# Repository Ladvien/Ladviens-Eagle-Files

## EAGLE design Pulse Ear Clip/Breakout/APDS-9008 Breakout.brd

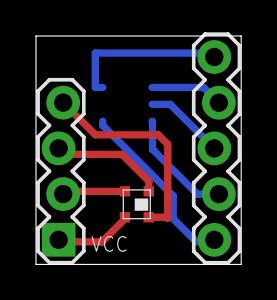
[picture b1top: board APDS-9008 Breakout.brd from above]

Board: 2 copper layers, 11.4 x 12.7 mm, 4 parts (1 on the bottom side), 9 nets.

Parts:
JP1: 1X04_LOCK
JP2: 1X05_LOCK
U$1: APDS9008
U$2: MCP6001UT-E/OT; SOT95P270X145-5N

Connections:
A-GND: JP1.3, U$1.GND
A-NC: JP1.4, U$1.NCC1
A-OUT: JP1.2, U$1.OUT
A-VCC: JP1.1, U$1.VCC
M-VDD: JP2.5, U$2.5
M-VIN+: JP2.2, U$2.3
M-VIN-: JP2.1, U$2.4
M-VOUT: JP2.4, U$2.1
M-VSS: JP2.3, U$2.2

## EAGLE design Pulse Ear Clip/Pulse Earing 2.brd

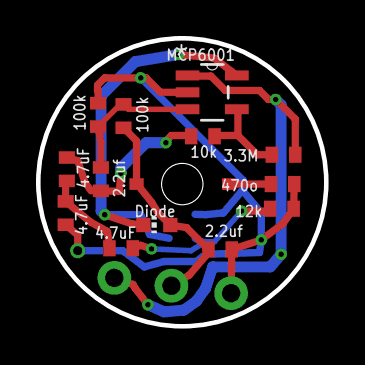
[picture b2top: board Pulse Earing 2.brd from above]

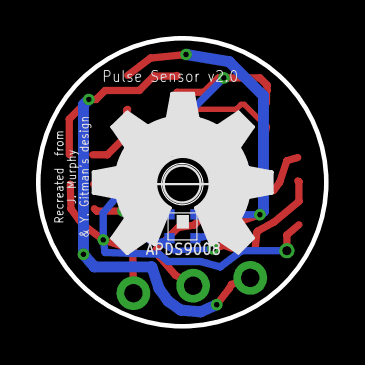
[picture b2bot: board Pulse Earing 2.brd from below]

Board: 2 copper layers, 16.0 x 16.0 mm, 19 parts (3 on the bottom side), 10 nets.

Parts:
+V: M01SMDNS; 1X01NS
C1, C4: 2.2uf; C0402
C2, C3, C5: 4.7uf; C0402
GND: M01SMDNS; 1X01NS
LED1: CHIP-LED0603
OUT: M01SMDNS; 1X01NS
R1: 10k; R0402
R2, R3: 100k; R0402
R4: 12k; R0402
R5: 470; R0402
R6: 3.3m; R0402
U$1: MCP6001UT-E/OT; SOT95P270X145-5N
U$2: APDS9008
U$3: KBREVMTNLED; KBREVMNTLED
U$4: OSHW_FILLX350_NOTEXT

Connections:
+V: +V.1, C1.1, LED1.A, R2.2, U$3.V+
unnamed: LED1.C, U$1.5, U$2.VCC
unnamed: R1.2, R6.1, U$1.4
unnamed: C2.1, R4.2, U$2.OUT
unnamed: C2.2, C3.1, C5.1
unnamed: C3.2, C4.1, R1.1
unnamed: C4.2, R2.1, R3.2, U$1.3
unnamed: R5.2, U$3.GND
unnamed: C1.2, C5.2, GND.1, R3.1, R4.1, R5.1, U$1.2, U$2.GND
OUT: OUT.1, R6.2, U$1.1

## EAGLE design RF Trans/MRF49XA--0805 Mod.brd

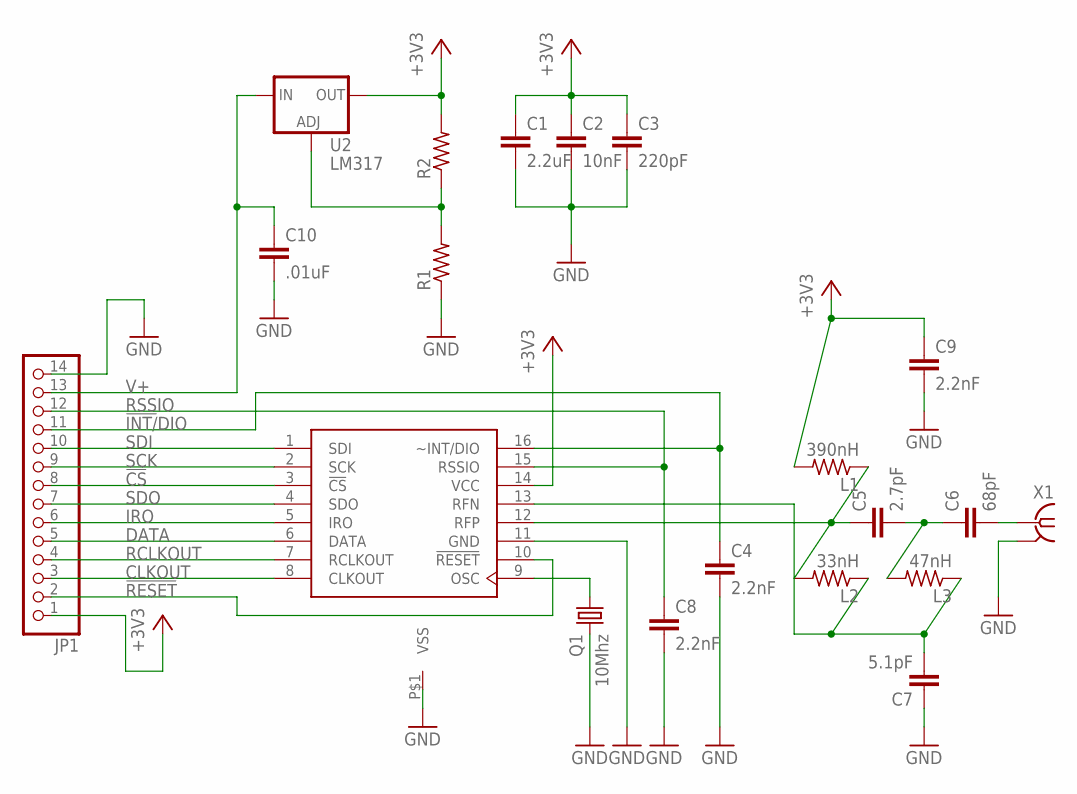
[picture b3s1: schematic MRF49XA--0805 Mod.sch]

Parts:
C1: 2.2uF; C0805
C2: 10nF; C0805
C3: 220pF; C0805
C4, C8, C9: 2.2nF; C0805
C5: 2.7pF; C0805
C6: 68pF; C0805
C7: 5.1pF; C0805
C10: .01uF; C0805
JP1: PINHD-1X14; 1X14
L1: 390nH; R0805
L2: 33nH; R0805
L3: 47nH; R0805
Q1: 10Mhz; CTS406
R1, R2: R-US_M0805; M0805
U2: LM317; SOT223
U$1: MRF49XA; TSSOP16
X1: SMA-142-0701-871/876; J502-ND-142-0701-871/876

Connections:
!CS: JP1.8, U$1.3 (!CS)
!INT/!DIO: C4.1, JP1.11, U$1.16 (~INT/DIO)
!RESET: JP1.2, U$1.10 (!RESET)
+3V3: C1.1, C2.1, C3.1, C9.1, JP1.1, L1.2, R2.2, U2.2 (OUT), U$1.14 (VCC)
CLKOUT: JP1.3, U$1.8 (CLKOUT)
DATA: JP1.5, U$1.6 (DATA)
GND: C1.2, C2.2, C3.2, C4.2, C7.1, C8.2, C9.2, C10.2, JP1.14, Q1.3 (2), R1.1, U$1.11 (GND), U$1.P$1 (VSS), X1.G@1 (GND), X1.G@2 (GND), X1.G@3 (GND), X1.G@4 (GND)
IRO: JP1.6, U$1.5 (IRO)
unnamed: Q1.1, U$1.9 (OSC)
unnamed: C5.2, C6.1, L3.2
unnamed: C6.2, X1.1
unnamed: C7.2, L2.1, L3.1, U$1.13 (RFN)
unnamed: C5.1, L1.1, L2.2, U$1.12 (RFP)
unnamed: R1.2, R2.1, U2.1 (ADJ)
RCLKOUT: JP1.4, U$1.7 (RCLKOUT)
RSSIO: C8.1, JP1.12, U$1.15 (RSSIO)
SCK: JP1.9, U$1.2 (SCK)
SDI: JP1.10, U$1.1 (SDI)
SDO: JP1.7, U$1.4 (SDO)
V+: C10.1, JP1.13, U2.3 (IN)

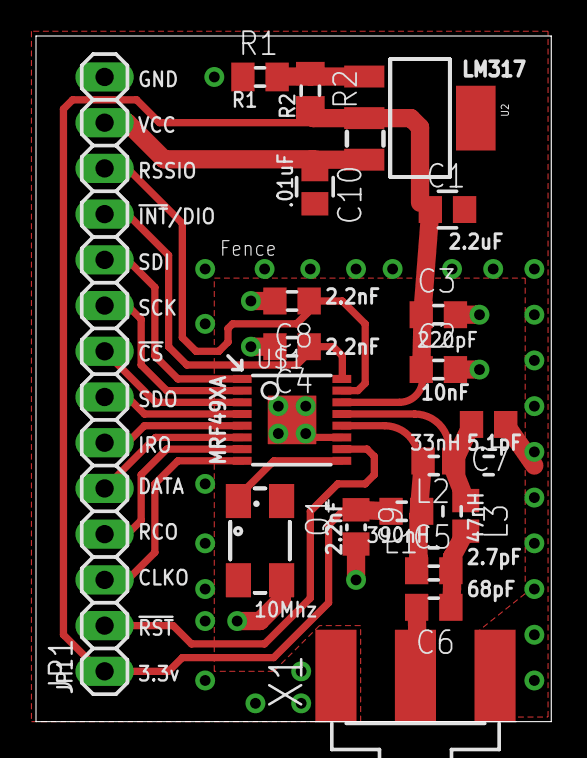
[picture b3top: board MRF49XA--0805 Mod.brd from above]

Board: 2 copper layers, 28.6 x 38.1 mm, 20 parts (0 on the bottom side), 20 nets.

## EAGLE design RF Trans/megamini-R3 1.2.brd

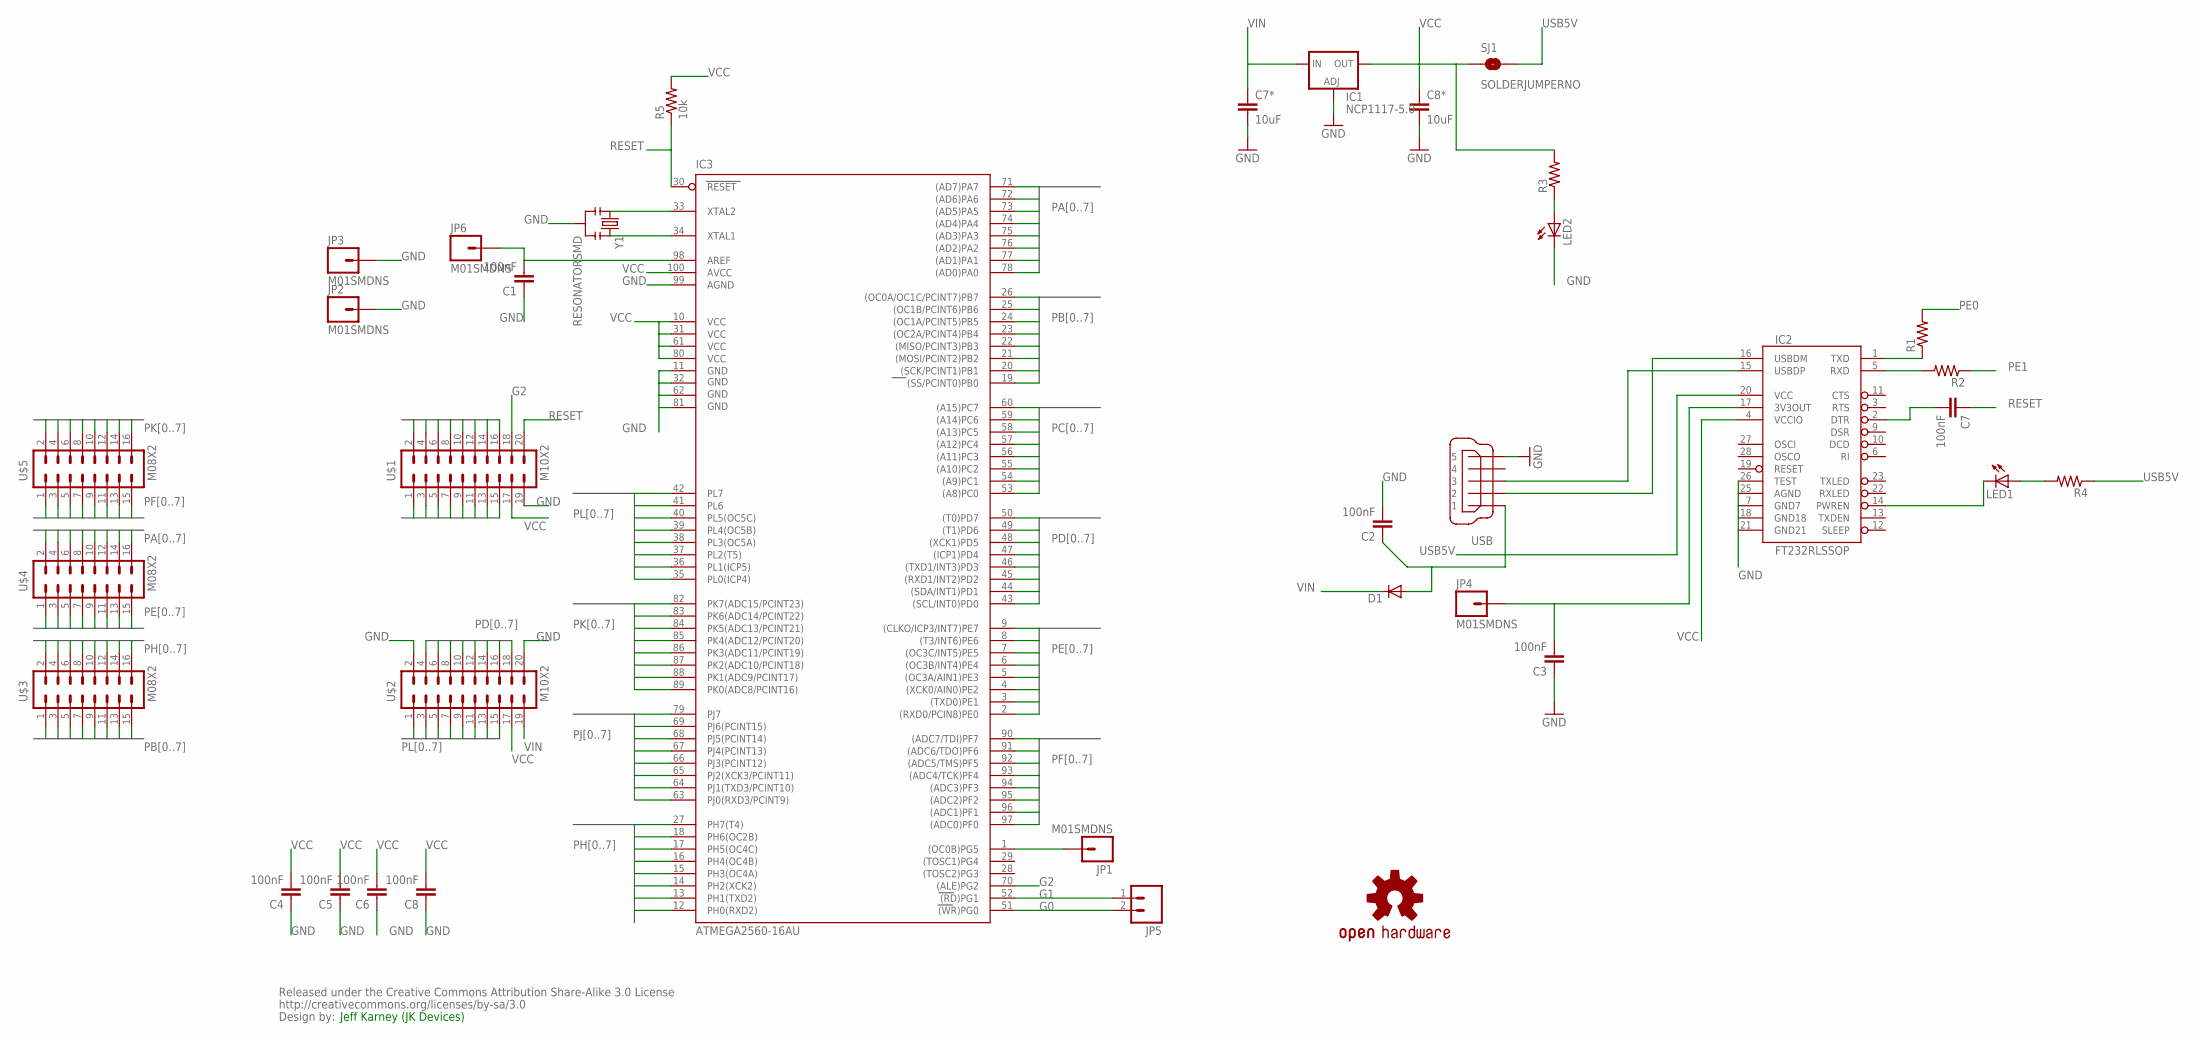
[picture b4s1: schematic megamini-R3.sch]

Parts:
C1, C2, C3, C4, C5, C6, C7, C8: 100nF; 0805
C7*, C8*: 10uF; 0805
D1: DIODESOD; SOD-323
IC1: NCP1117-5.0; DPACK
IC2: FT232RLSSOP; SSOP28DB
IC3: ATMEGA2560-16AU; TQFP100
JP1, JP2, JP3, JP4, JP6: M01SMDNS; 1X01NS
JP5: M02PTH; 1X02
LED1, LED2: LED0603; LED-0603
R1, R2, R3, R4: RESISTOR0805-RES; 0805
R5: 10k; 0805
SJ1: SOLDERJUMPERNO; SJ_2S-NO
U$1, U$2: M10X2; 2X10
U$3, U$4, U$5: M08X2; 2X8_SMALL
U$6: OSHW-LOGOS; OSHW-LOGO-S
U$7: CREATIVE_COMMONS
USB: MINI-USB-UX60-MB-5ST; UX60-MB-5ST
Y1: RESONATORSMD; RESONATOR-SMD

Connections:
G0: IC3.51 ((WR)PG0), JP5.2
G1: IC3.52 ((RD)PG1), JP5.1
G2: IC3.70 ((ALE)PG2), U$1.18
GND: C1.1, C2.2, C3.1, C4.1, C5.1, C6.1, C7*.2, C8.1, C8*.2, IC1.1 (ADJ), IC2.7 (GND7), IC2.18 (GND18), IC2.21 (GND21), IC2.25 (AGND), IC2.26 (TEST), IC3.11 (GND), IC3.32 (GND1), IC3.62 (GND2), IC3.81 (GND3), IC3.99 (AGND), JP2.1, JP3.1, LED2.C, U$1.19, U$2.2, U$2.20, USB.5, Y1.2
unnamed: IC2.16 (USBDM), USB.2
unnamed: IC3.1 ((OC0B)PG5), JP1.1
unnamed: IC2.15 (USBDP), USB.3
unnamed: C7.2, IC2.2 (DTR)
unnamed: IC2.1 (TXD), R1.1
unnamed: IC2.5 (RXD), R2.2
unnamed: C3.2, IC2.17 (3V3OUT), JP4.1
unnamed: IC3.33 (XTAL2), Y1.1
unnamed: IC3.34 (XTAL1), Y1.3
unnamed: LED2.A, R3.1
unnamed: LED1.A, R4.2
unnamed: IC2.14 (PWREN), LED1.C
unnamed: C1.2, IC3.98 (AREF), JP6.1
PA0: IC3.78 ((AD0)PA0), U$4.2
PA1: IC3.77 ((AD1)PA1), U$4.4
PA2: IC3.76 ((AD2)PA2), U$4.6
PA3: IC3.75 ((AD3)PA3), U$4.8
PA4: IC3.74 ((AD4)PA4), U$4.10
PA5: IC3.73 ((AD5)PA5), U$4.12
PA6: IC3.72 ((AD6)PA6), U$4.14
PA7: IC3.71 ((AD7)PA7), U$4.16
PB0: IC3.19 ((SS/PCINT0)PB0), U$3.15
PB1: IC3.20 ((SCK/PCINT1)PB1), U$3.13
PB2: IC3.21 ((MOSI/PCINT2)PB2), U$3.11
PB3: IC3.22 ((MISO/PCINT3)PB3), U$3.9
PB4: IC3.23 ((OC2A/PCINT4)PB4), U$3.7
PB5: IC3.24 ((OC1A/PCINT5)PB5), U$3.5
PB6: IC3.25 ((OC1B/PCINT6)PB6), U$3.3
PB7: IC3.26 ((OC0A/OC1C/PCINT7)PB7), U$3.1
PC0: IC3.53 ((A8)PC0), U$1.15
PC1: IC3.54 ((A9)PC1), U$1.13
PC2: IC3.55 ((A10)PC2), U$1.11
PC3: IC3.56 ((A11)PC3), U$1.9
PC4: IC3.57 ((A12)PC4), U$1.7
PC5: IC3.58 ((A13)PC5), U$1.5
PC6: IC3.59 ((A14)PC6), U$1.3
PC7: IC3.60 ((A15)PC7), U$1.1
PD0: IC3.43 ((SCL/INT0)PD0), U$2.4
PD1: IC3.44 ((SDA/INT1)PD1), U$2.6
PD2: IC3.45 ((RXD1/INT2)PD2), U$2.8
PD3: IC3.46 ((TXD1/INT3)PD3), U$2.10
PD4: IC3.47 ((ICP1)PD4), U$2.12
PD5: IC3.48 ((XCK1)PD5), U$2.14
PD6: IC3.49 ((T1)PD6), U$2.16
PD7: IC3.50 ((T0)PD7), U$2.18
PE0: IC3.2 ((RXD0/PCIN8)PE0), R1.2, U$4.15
PE1: IC3.3 ((TXD0)PE1), R2.1, U$4.13
PE2: IC3.4 ((XCK0/AIN0)PE2), U$4.11
PE3: IC3.5 ((OC3A/AIN1)PE3), U$4.9
PE4: IC3.6 ((OC3B/INT4)PE4), U$4.7
PE5: IC3.7 ((OC3C/INT5)PE5), U$4.5
PE6: IC3.8 ((T3/INT6)PE6), U$4.3
PE7: IC3.9 ((CLKO/ICP3/INT7)PE7), U$4.1
PF0: IC3.97 ((ADC0)PF0), U$5.15
PF1: IC3.96 ((ADC1)PF1), U$5.13
PF2: IC3.95 ((ADC2)PF2), U$5.11
PF3: IC3.94 ((ADC3)PF3), U$5.9
PF4: IC3.93 ((ADC4/TCK)PF4), U$5.7
PF5: IC3.92 ((ADC5/TMS)PF5), U$5.5
PF6: IC3.91 ((ADC6/TDO)PF6), U$5.3
PF7: IC3.90 ((ADC7/TDI)PF7), U$5.1
PH0: IC3.12 (PH0(RXD2)), U$3.16
PH1: IC3.13 (PH1(TXD2)), U$3.14
PH2: IC3.14 (PH2(XCK2)), U$3.12
PH3: IC3.15 (PH3(OC4A)), U$3.10
PH4: IC3.16 (PH4(OC4B)), U$3.8
PH5: IC3.17 (PH5(OC4C)), U$3.6
PH6: IC3.18 (PH6(OC2B)), U$3.4
PH7: IC3.27 (PH7(T4)), U$3.2
PJ0: IC3.63 (PJ0(RXD3/PCINT9)), U$1.2
PJ1: IC3.64 (PJ1(TXD3/PCINT10)), U$1.4
PJ2: IC3.65 (PJ2(XCK3/PCINT11)), U$1.6
PJ3: IC3.66 (PJ3(PCINT12)), U$1.8
PJ4: IC3.67 (PJ4(PCINT13)), U$1.10
PJ5: IC3.68 (PJ5(PCINT14)), U$1.12
PJ6: IC3.69 (PJ6(PCINT15)), U$1.14
PJ7: IC3.79 (PJ7), U$1.16
PK0: IC3.89 (PK0(ADC8/PCINT16)), U$5.16
PK1: IC3.88 (PK1(ADC9/PCINT17)), U$5.14
PK2: IC3.87 (PK2(ADC10/PCINT18)), U$5.12
PK3: IC3.86 (PK3(ADC11/PCINT19)), U$5.10
PK4: IC3.85 (PK4(ADC12/PCINT20)), U$5.8
PK5: IC3.84 (PK5(ADC13/PCINT21)), U$5.6
PK6: IC3.83 (PK6(ADC14/PCINT22)), U$5.4
PK7: IC3.82 (PK7(ADC15/PCINT23)), U$5.2
PL0: IC3.35 (PL0(ICP4)), U$2.1
PL1: IC3.36 (PL1(ICP5)), U$2.3
PL2: IC3.37 (PL2(T5)), U$2.5
PL3: IC3.38 (PL3(OC5A)), U$2.7
PL4: IC3.39 (PL4(OC5B)), U$2.9
PL5: IC3.40 (PL5(OC5C)), U$2.11
PL6: IC3.41 (PL6), U$2.13
PL7: IC3.42 (PL7), U$2.15
RESET: C7.1, IC3.30 (RESET), R5.1, U$1.20
USB5V: C2.1, D1.2 (A), IC2.20 (VCC), R4.1, SJ1.2, USB.1
VCC: C4.2, C5.2, C6.2, C8.2, C8*.1, IC1.4 (OUT), IC2.4 (VCCIO), IC3.10 (VCC), IC3.31 (VCC1), IC3.61 (VCC2), IC3.80 (VCC3), IC3.100 (AVCC), R3.2, R5.2, SJ1.1, U$1.17, U$2.17
VIN: C7*.1, D1.1 (C), IC1.3 (IN), U$2.19

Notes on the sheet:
Jeff Karney (JK Devices)

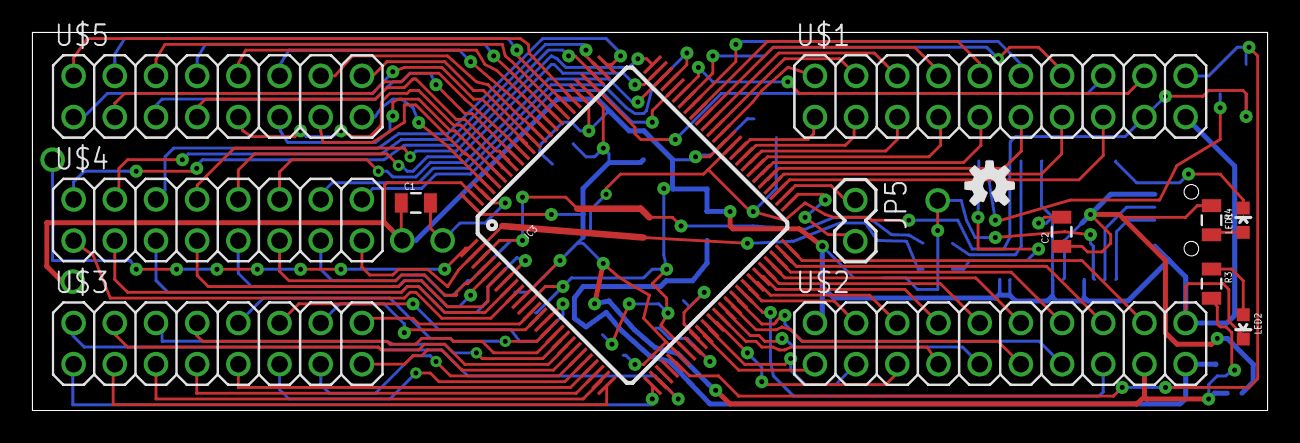
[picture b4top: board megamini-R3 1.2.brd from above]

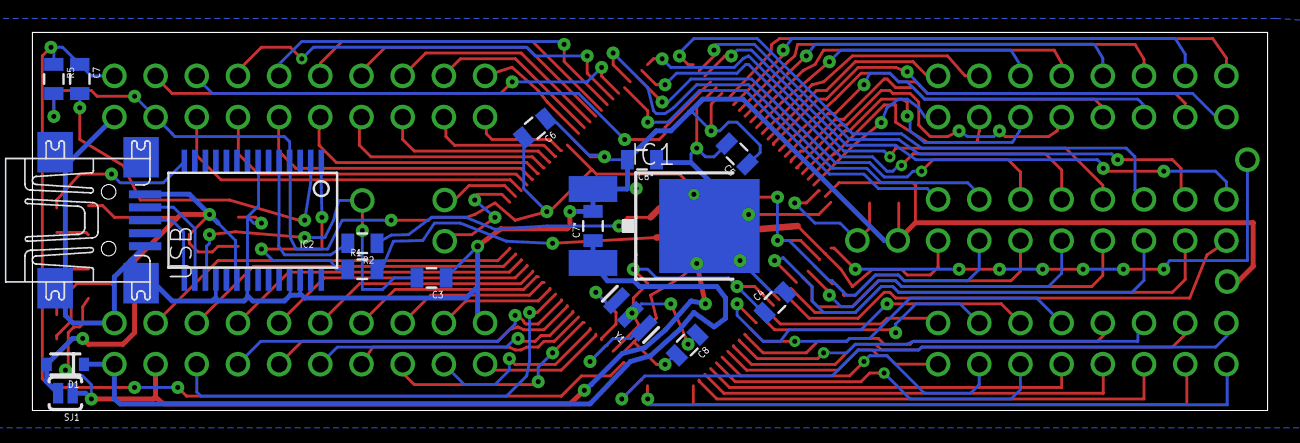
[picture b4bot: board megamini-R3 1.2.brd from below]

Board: 2 copper layers, 76.2 x 23.3 mm, 37 parts (17 on the bottom side), 101 nets.

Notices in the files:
RF Trans/MRF49XA--0805 Mod.brd:
(C) 2010 - William Dillon KD7VMY
Licensed under the
TAPR Open Hardware License
RF Trans/megamini-R3 1.2.brd:
(C)2011 JK Devices
CC-BY-SA 3.0
parts and their libraries:
SparkFun: Licensing: CC v3.0 Share-Alike You are welcome to use this library for commercial purposes.
SparkFun: Released under the Creative Commons Attribution Share-Alike 3.0 License
SparkFun: http://creativecommons.org/licenses/by-sa/3.0
